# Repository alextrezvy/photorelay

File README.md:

# photorelay

PCB in KiCad format.
Based on: http://sxemkin.ru/?p=1738 .

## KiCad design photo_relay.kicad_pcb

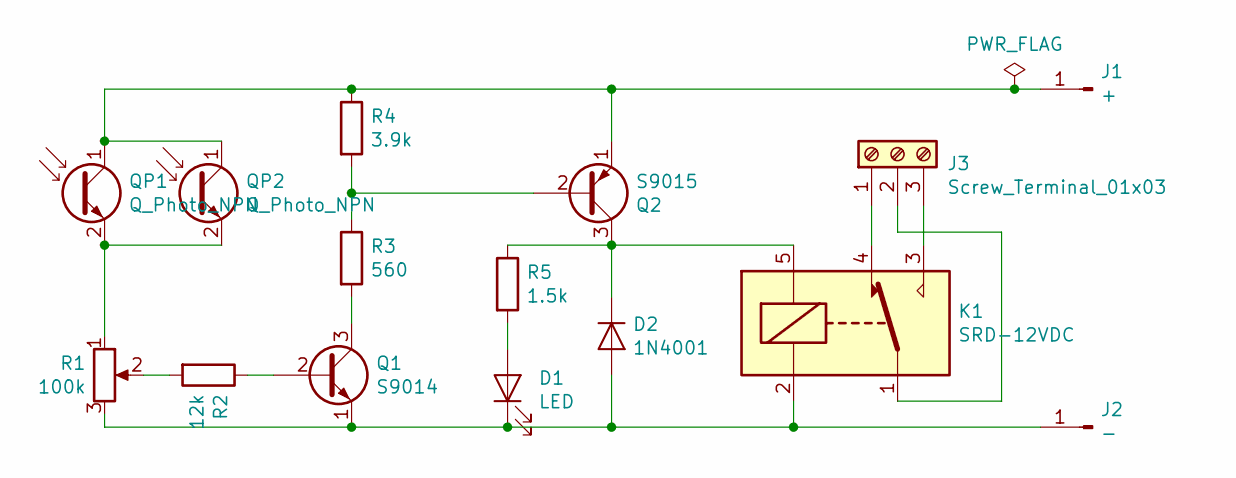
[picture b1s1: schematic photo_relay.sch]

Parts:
D1: LED; LED_D3.0mm
D2: 1N4001; D_A-405_P7.62mm_Horizontal
J1: +; SolderWirePad_1x01_Drill1.5mm
J2: -; SolderWirePad_1x01_Drill1.5mm
J3: Screw_Terminal_01x03; TerminalBlock_bornier-3_P5.08mm
K1: SRD-12VDC; Relay_SPDT_SANYOU_SRD_Series_Form_C
Q1: S9014; TO-92
Q2: S9015; TO-92
QP1, QP2: Q_Photo_NPN; LED_D3.0mm
R1: 100k; Potentiometer_ACP_CA14-H4_Horizontal
R2: 12k; R_Axial_DIN0207_L6.3mm_D2.5mm_P10.16mm_Horizontal
R3: 560; R_Axial_DIN0207_L6.3mm_D2.5mm_P10.16mm_Horizontal
R4: 3.9k; R_Axial_DIN0207_L6.3mm_D2.5mm_P10.16mm_Horizontal
R5: 1.5k; R_Axial_DIN0207_L6.3mm_D2.5mm_P5.08mm_Vertical

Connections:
unnamed: D1.1 (K), D2.2 (A), J2.1, K1.2, Q1.1 (E), R1.3
unnamed: D1.2 (A), R5.2
unnamed: D2.1 (K), K1.5, Q2.3 (C), R5.1
unnamed: J1.1, Q2.1 (E), QP1.1 (C), QP2.1 (C), R4.1
unnamed: J3.1, K1.4
unnamed: J3.2, K1.1
unnamed: J3.3, K1.3
unnamed: Q1.2 (B), R2.1
unnamed: Q1.3 (C), R3.2
unnamed: Q2.2 (B), R3.1, R4.2
unnamed: QP1.2 (E), QP2.2 (E), R1.1
unnamed: R1.2, R2.2

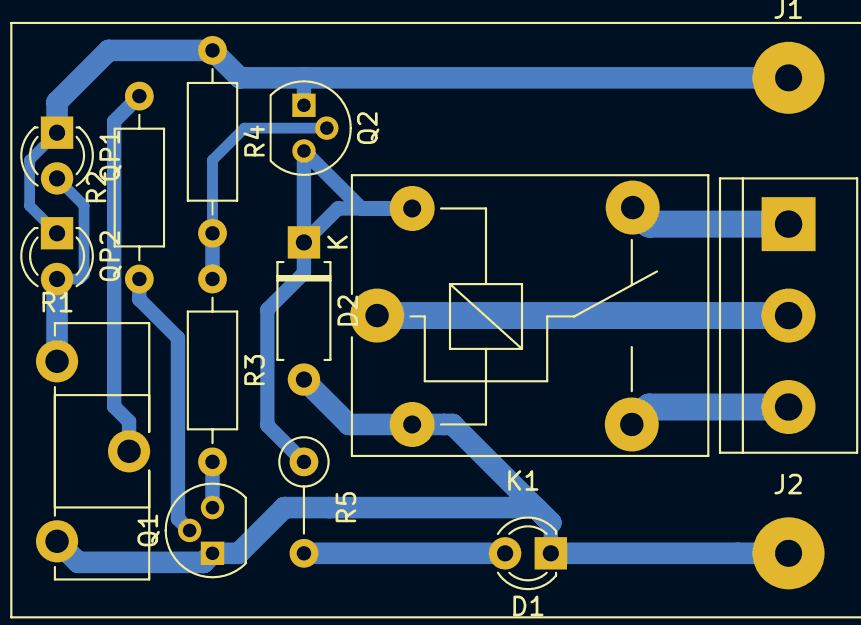
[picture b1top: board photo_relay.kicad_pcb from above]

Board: 2 copper layers, 15 parts (0 on the bottom side), 12 nets.

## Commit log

2020-03-23 corrected typo
